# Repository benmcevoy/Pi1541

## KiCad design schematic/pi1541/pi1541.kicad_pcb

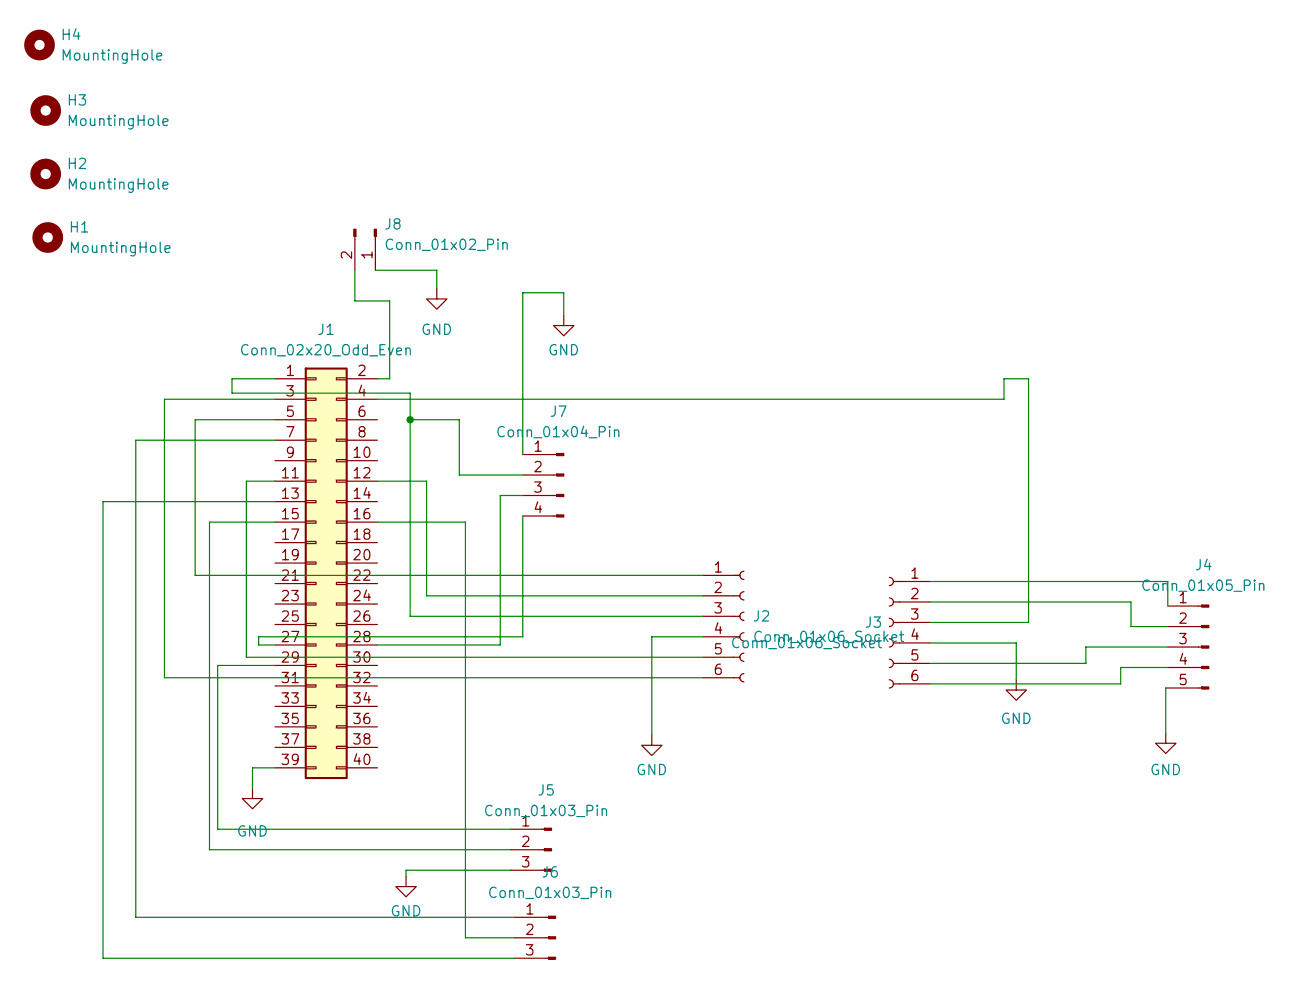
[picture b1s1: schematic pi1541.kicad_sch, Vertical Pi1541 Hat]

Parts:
H1, H2, H3, H4: MountingHole; MountingHole_2.7mm_M2.5
J1: Conn_02x20_Odd_Even; PinHeader_2x20_P2.54mm_Vertical
J2, J3: Conn_01x06_Socket; PinHeader_1x06_P2.54mm_Vertical
J4: Conn_01x05_Pin; PinHeader_1x05_P2.54mm_Vertical
J5, J6: Conn_01x03_Pin; PinHeader_1x03_P2.54mm_Vertical_Nav
J7: Conn_01x04_Pin; PinHeader_1x04_P2.54mm_Vertical
J8: Conn_01x02_Pin; PinHeader_1x02_P2.54mm_Vertical

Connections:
GND: J1.39, J2.4, J3.4, J4.5, J5.3, J7.1, J8.1
unnamed: J1.1, J2.3, J7.2
unnamed: J1.2, J8.2
unnamed: J1.3, J2.6
unnamed: J1.4, J3.3
unnamed: J1.5, J2.1
unnamed: J1.7, J6.1
unnamed: J1.11, J2.5
unnamed: J1.12, J2.2
unnamed: J1.13, J6.3
unnamed: J1.15, J5.2
unnamed: J1.16, J6.2
unnamed: J1.27, J7.4
unnamed: J1.28, J7.3
unnamed: J1.29, J5.1
unnamed: J3.1, J4.1
unnamed: J3.2, J4.2
unnamed: J3.5, J4.3
unnamed: J3.6, J4.4

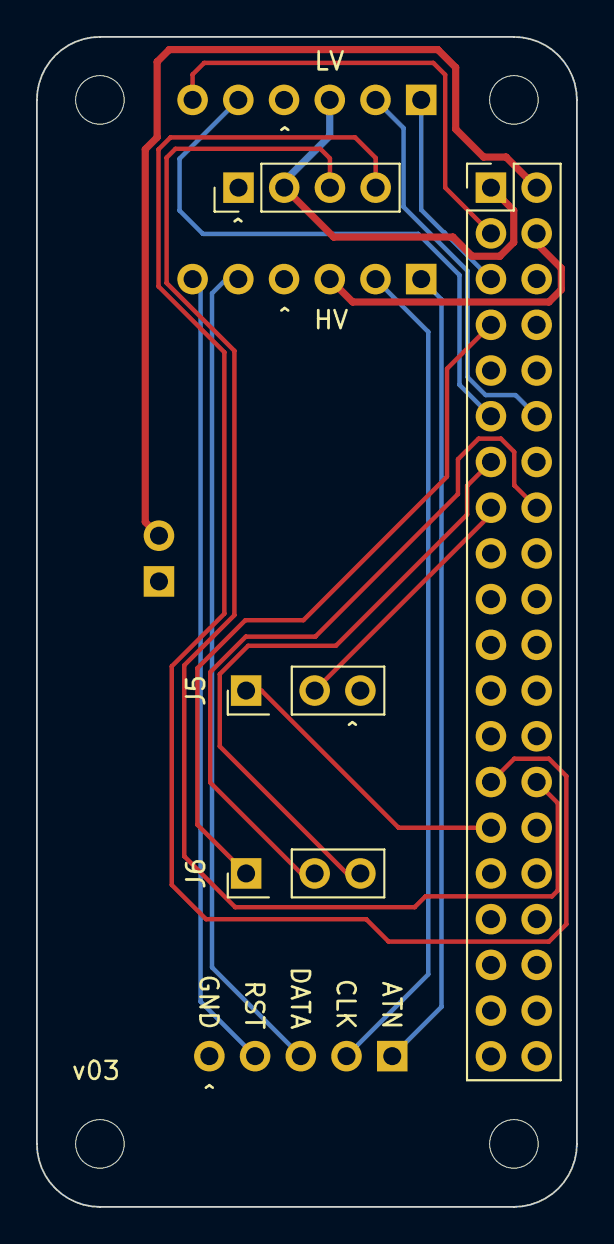
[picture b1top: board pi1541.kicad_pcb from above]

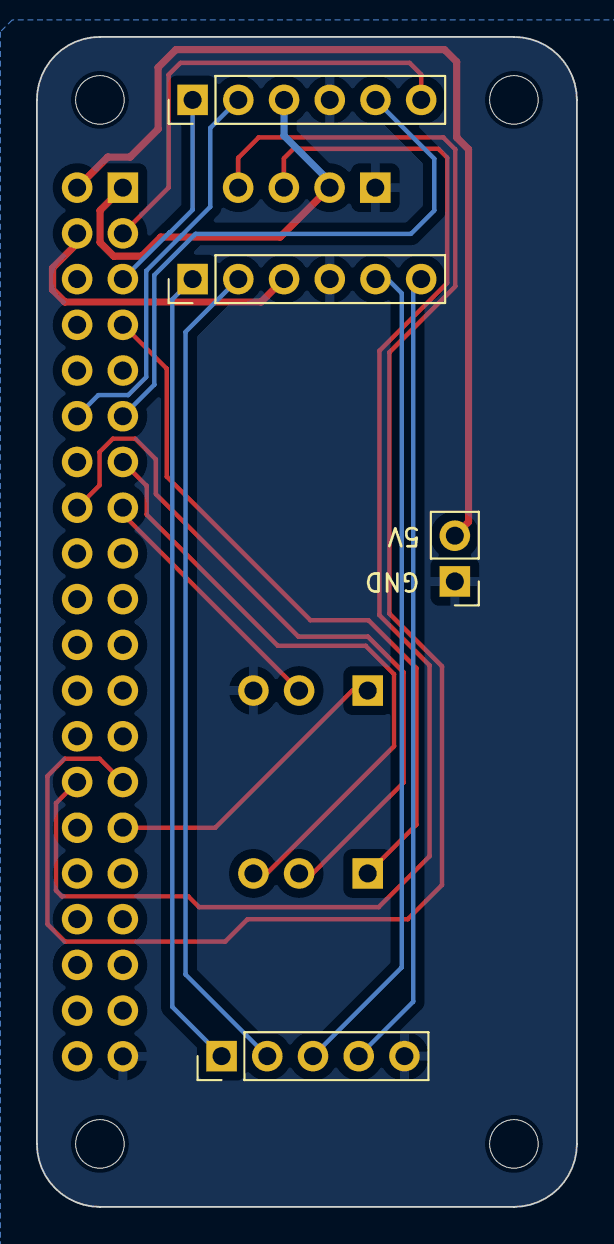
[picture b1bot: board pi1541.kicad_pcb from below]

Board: 2 copper layers, 30.0 x 65.0 mm, 12 parts (4 on the bottom side), 19 nets.

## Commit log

2023-11-26 schematic
